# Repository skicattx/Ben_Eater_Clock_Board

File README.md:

# Ben_Eater_Clock_Board
Circuit Board based on Ben Eater's Variable and Manual clock circuit design

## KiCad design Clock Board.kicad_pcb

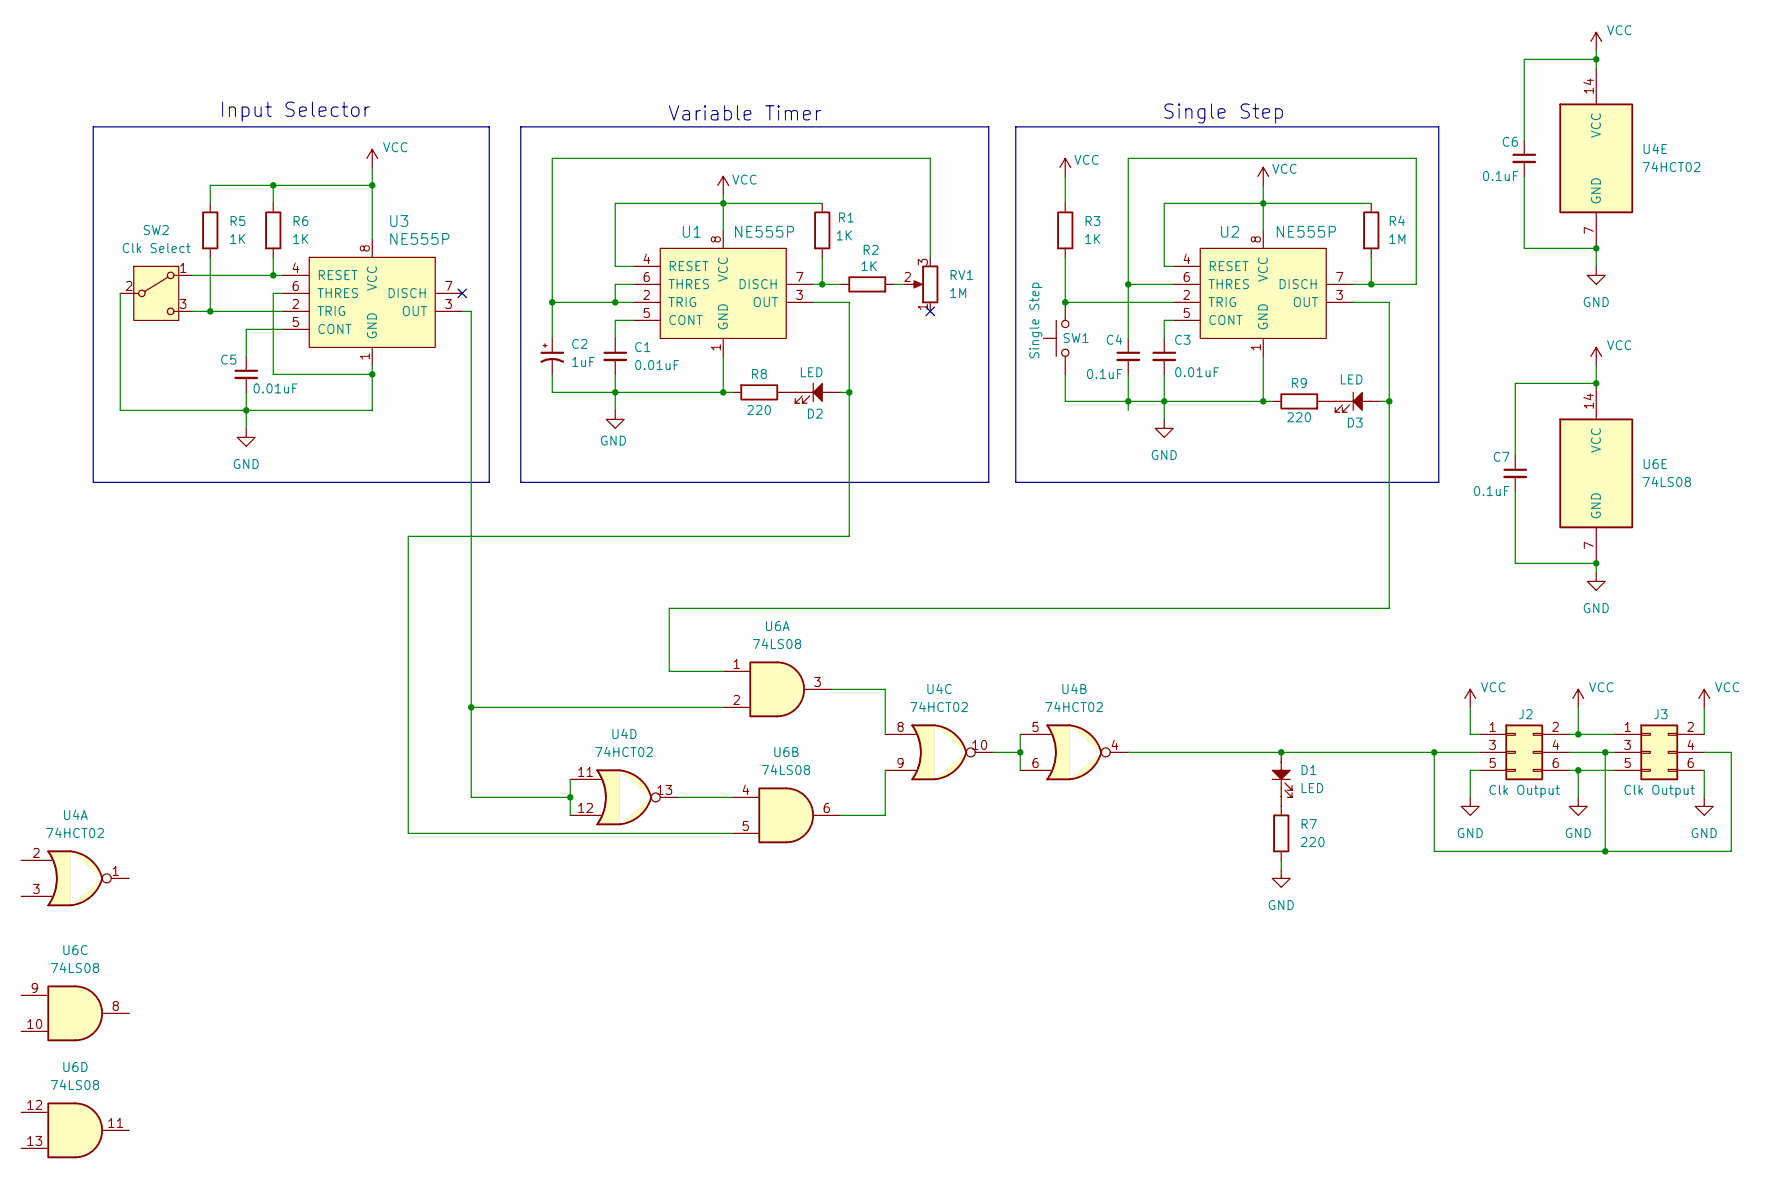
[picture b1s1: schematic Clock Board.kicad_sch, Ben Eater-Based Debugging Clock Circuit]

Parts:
C1, C3, C5: 0.01uF; C_Disc_D5.0mm_W2.5mm_P5.00mm
C2: 1uF; CP_Radial_D5.0mm_P2.00mm
C4, C6, C7: 0.1uF; C_Disc_D5.0mm_W2.5mm_P5.00mm
D1, D2, D3: LED; LED_D5.0mm
J2: Clk Output; PinSocket_2x03_P2.54mm_Vertical
J3: Clk Output; PinHeader_2x03_P2.54mm_Vertical
R1, R2, R3, R5, R6: 1K; R_Axial_DIN0207_L6.3mm_D2.5mm_P10.16mm_Horizontal
R4: 1M; R_Axial_DIN0207_L6.3mm_D2.5mm_P10.16mm_Horizontal
R7, R8, R9: 220; R_Axial_DIN0207_L6.3mm_D2.5mm_P10.16mm_Horizontal
RV1: 1M; Potentiometer_TT_P0915N
SW1: Single Step; Terminal_Block_D1.3mm_P5mm
SW2: Clk Select; SW_Slide_SPDT_Straight_CK_OS102011MS2Q
U1, U2, U3: NE555P; DIP-8_W7.62mm_Socket; MPN NE555P; Digi-Key_PN 296-1411-5-ND
U4: 74HCT02; DIP-14_W7.62mm_Socket
U6: 74LS08; DIP-14_W7.62mm_Socket

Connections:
GND: C1.2, C2.2, C3.2, C4.2, C5.2, C6.2, C7.2, J2.5, J2.6, J3.5, J3.6, R7.2, R8.2, R9.1, SW1.1, SW2.2 (B), U1.1 (GND), U2.1 (GND), U3.1 (GND), U3.6 (THRES), U4.7 (GND), U6.7 (GND)
unnamed: D1.1, R7.1
unnamed: D2.1, R8.1
unnamed: D3.1, R9.2
unnamed: D1.2, J2.3, J2.4, J3.3, J3.4, U4.4
unnamed: R2.2, RV1.2
unnamed: R6.2, SW2.1 (A), U3.4 (RESET)
unnamed: R5.2, SW2.3 (C), U3.2 (TRIG)
unnamed: C1.1, U1.5 (CONT)
unnamed: R1.2, R2.1, U1.7 (DISCH)
unnamed: D2.2, U1.3 (OUT), U6.5
unnamed: C2.1, RV1.3, U1.2 (TRIG), U1.6 (THRES)
unnamed: C3.1, U2.5 (CONT)
unnamed: C4.1, R4.2, U2.6 (THRES), U2.7 (DISCH)
unnamed: D3.2, U2.3 (OUT), U6.1
unnamed: R3.2, SW1.2, U2.2 (TRIG)
unnamed: C5.1, U3.5 (CONT)
unnamed: U3.3 (OUT), U4.11, U4.12, U6.2
unnamed: U4.8, U6.3
unnamed: U4.9, U6.6
unnamed: U4.5, U4.6, U4.10
unnamed: U4.13, U6.4
VCC: C6.1, C7.1, J2.1, J2.2, J3.1, J3.2, R1.1, R3.1, R4.1, R5.1, R6.1, U1.4 (RESET), U1.8 (VCC), U2.4 (RESET), U2.8 (VCC), U3.8 (VCC), U4.14 (VCC), U6.14 (VCC)

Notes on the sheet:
Single Step
Input Selector
Variable Timer

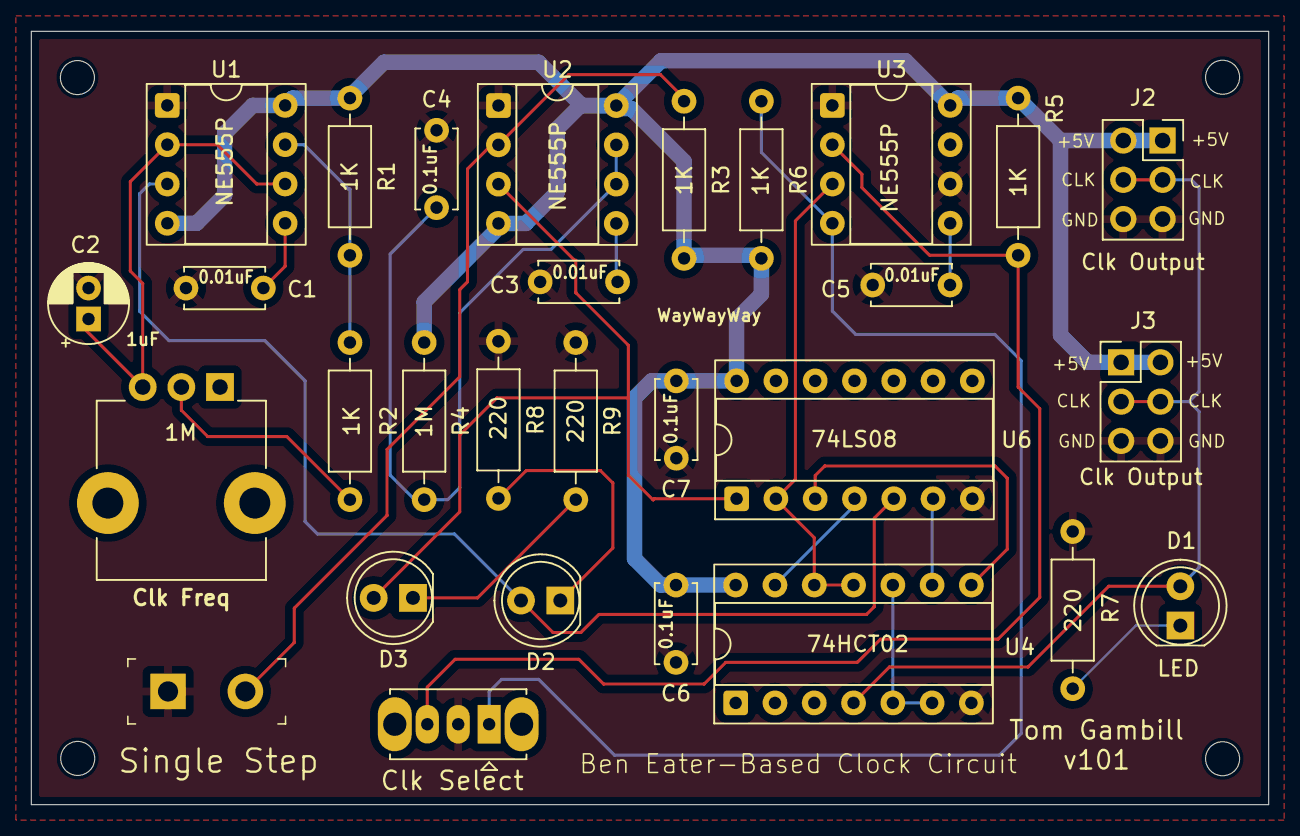
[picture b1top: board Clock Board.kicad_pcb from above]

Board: 2 copper layers, 80.0 x 50.0 mm, 33 parts (0 on the bottom side), 23 nets.

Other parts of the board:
Ref1, Ref2, Ref3, Ref4: MountingHole_2.2mm_M2

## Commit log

2025-02-23 add ds store
2025-02-23 Initial schematic
2025-02-23 Rename
2025-02-23 First Pass
2025-02-25 PCB Work
2025-02-25 PCBWay - Initial Design Submitted
2025-03-05 Reverse diodes, increase text size on some labels
